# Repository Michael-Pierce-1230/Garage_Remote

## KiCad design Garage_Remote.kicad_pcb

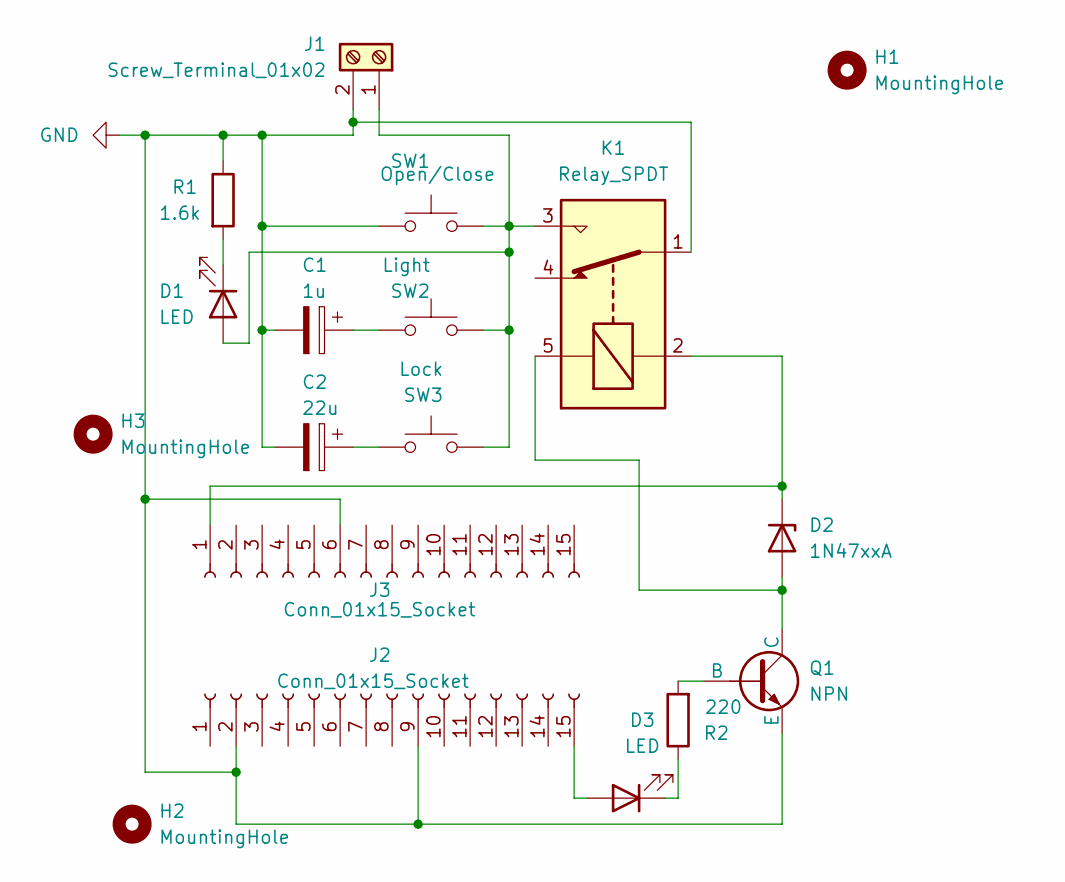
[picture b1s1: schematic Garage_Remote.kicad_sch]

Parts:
C1: 1u; CP_Radial_D6.3mm_P2.50mm
C2: 22u; CP_Radial_D6.3mm_P2.50mm
D1, D3: LED; LED_D3.0mm
D2: 1N47xxA; D_DO-41_SOD81_P10.16mm_Horizontal
H1, H2, H3: MountingHole; MountingHole_3.2mm_M3_Pad_TopOnly
J1: Screw_Terminal_01x02; TerminalBlock_Phoenix_MKDS-1,5-2-5.08_1x02_P5.08mm_Horizont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
J2, J3: Conn_01x15_Socket; PinSocket_1x15_P2.54mm_Vertical
K1: Relay_SPDT; Relay_SPDT_Omron-G5LE-1
Q1: NPN; SOT-23
R1: 1.6k; R_Axial_DIN0207_L6.3mm_D2.5mm_P10.16mm_Horizontal
R2: 220; R_Axial_DIN0207_L6.3mm_D2.5mm_P10.16mm_Horizontal
SW1: Open/Close; SW_PUSH_6mm
SW2: Light; SW_PUSH_6mm
SW3: Lock; SW_PUSH_6mm

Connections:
GND: C1.2, C2.2, J1.2, J2.2, J2.9, J3.6, K1.1, Q1.2 (E), R1.1, SW1.1
unnamed: C1.1, SW2.1
unnamed: C2.1, SW3.1
unnamed: D1.2 (A), J1.1, K1.3, SW1.2, SW2.2, SW3.2
unnamed: D1.1 (K), R1.2
unnamed: D2.2 (A), K1.5, Q1.3 (C)
unnamed: D2.1 (K), J3.1, K1.2
unnamed: D3.2 (A), J2.15
unnamed: D3.1 (K), R2.1
unnamed: Q1.1 (B), R2.2

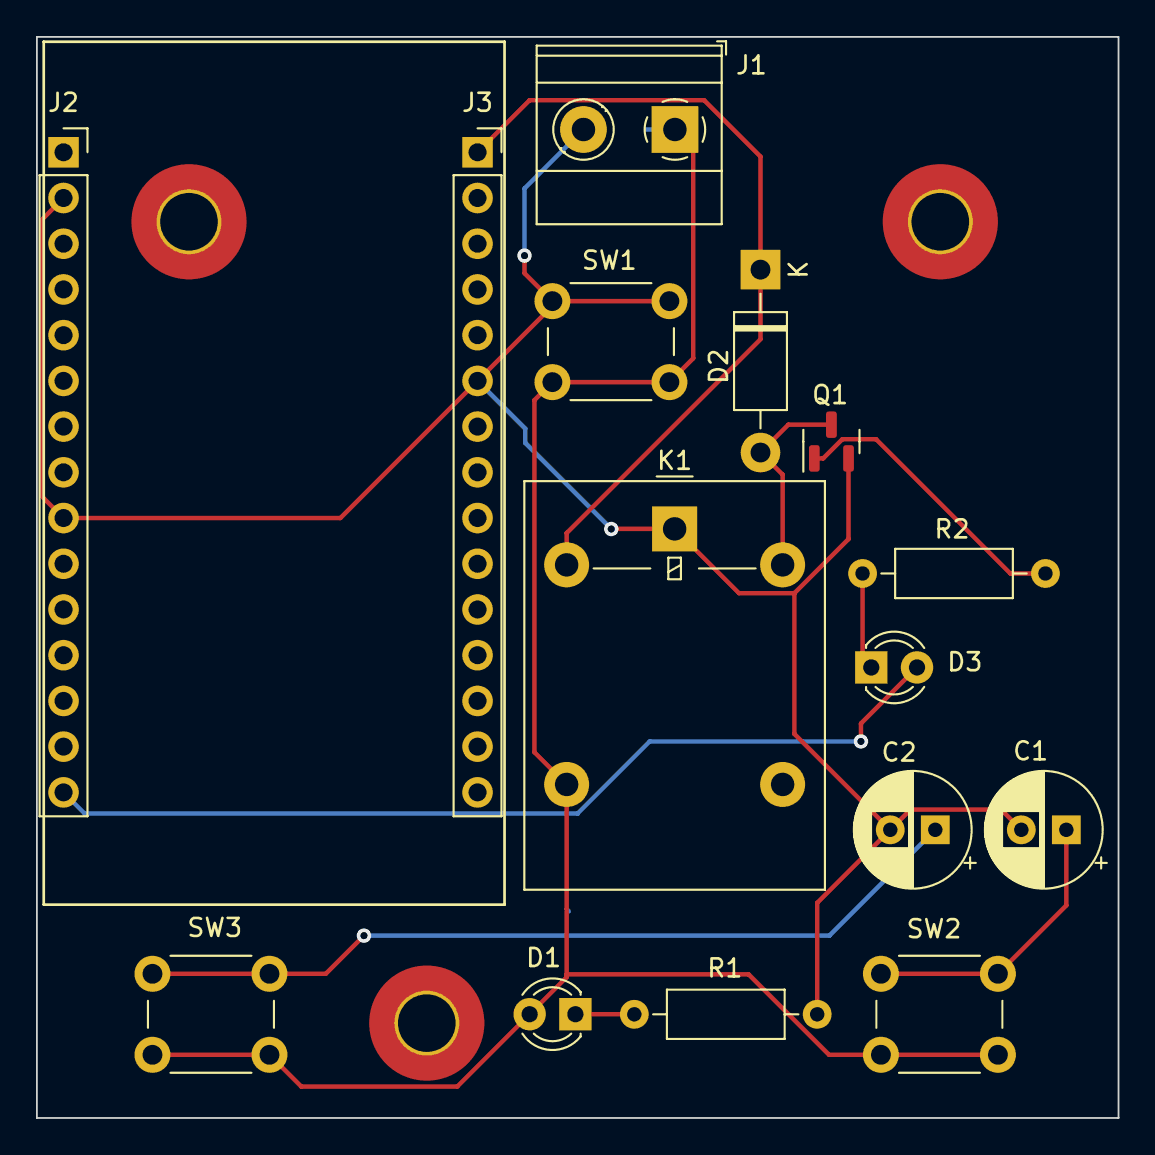
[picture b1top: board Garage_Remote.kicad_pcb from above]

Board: 2 copper layers, 60.1 x 60.1 mm, 18 parts (0 on the bottom side), 10 nets.

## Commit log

2023-12-27 Ki Kad garage remote files
2023-12-27 Ki Kad garage remote png file
